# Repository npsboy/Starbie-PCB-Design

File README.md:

# Starbie

A small KiCad PCB project: a handheld board built around a Seeed XIAO ESP32-C3, with an I2C OLED display (128x64), an MPU6050 motion sensor (GY-521), and push buttons (Cherry MX switches).

## What is it?

The Starbie is a handheld PCB with an embedded OLED display that acts as a digital pet. You can interact with the digital character using push buttons and using the gyroscope (motion sensor), which can detect tilts, shakes and so on.

## What each part does:
- XIAO ESP32C3: The main brain of the system. This is a small development board, kind of like a regular esp 32 or raspberri-pi pico, not a bare microcontroller processor.
- OLED: The main screen that displays the charecter/pet.
- Accelerometer/Gyro: Detects tilts, shakes, etc.
- Temperature and humidity sensor: Exactly what it says it does. Can be used later to trigger different animations for the pet based on the environmental conditions.
- Mechanical keyboard switches: These are the two push buttons that help us interact with the pet. These are not the standard push buttons that you usually see, though.
- MX Keycaps: The keyboard switches do not come with a keycap. You have to buy and attach it yourself, or clicking the buttons won't be very comfortable.

## Schematic

## 3D Render

## Bill of Materials

Full BOM with vendor links and notes: [Starbie_BOM.csv](Starbie_BOM.csv) (prices in USD, vendors in India).

| Part | Ref | Purpose | Qty | UNIT | Vendor |
| --- | --- | --- | --- | --- | --- |
| Seeed Studio XIAO ESP32C3 | U2 | Microcontroller (Wi-Fi, main loop) | 1 | 15.91 | [Amazon](https://www.amazon.in/dp/B0B94JZ2YF) |
| 0.96in 128x64 I2C OLED, 4-pin | J1 | Shows the pet and the menu | 1 | 1.68 | [Ktron](https://www.ktron.in/product/oled-display-i2c-0-96-inch/) |
| MPU6050 GY-521 accelerometer/gyro | J2 | Tilt to steer the menu, shake detection | 1 | 1.99 | [Ktron](https://www.ktron.in/product/mpu6050-module/) |
| DHT11 temperature/humidity sensor, bare 4-pin | U1 | Senses room temperature and humidity | 1 | 0.96 | [Ktron](https://www.ktron.in/product/dht11-temperature-and-humidity-sensor/) |
| MX-style mechanical keyboard switches | SW1, SW2 | The two buttons (menu and stats) | 1 pack | 8.28 | [Amazon](https://www.amazon.in/dp/B0G39H2G4H) |
| Blank MX keycaps | SW1, SW2 | Caps for the two buttons | 1 pack | 7.18 | [Amazon](https://www.amazon.in/dp/B0HD587C9N) |
| PCB fabrication, 2-layer FR4, 98.04x98.8 mm | | The bare Starbie board (Rs 2,166 for 5 boards, about Rs 433 each) | 1 order (5 boards) | 22.45 | [LionCircuits](https://www.lioncircuits.com/) |

## Contents

- `Starbie.kicad_sch` / `Starbie.kicad_pcb` / `Starbie.kicad_pro`: KiCad project files
- `libs/`: custom symbols, footprints and 3D models
- `gerbers/`, `Starbie_Gerbers.zip`: manufacturing outputs
- `Starbie_BOM.csv`: bill of materials with vendors and prices (India)
- `Starbie_CPL.csv`: component placement list for PCB assembly
- `renders/`: top and bottom board renders

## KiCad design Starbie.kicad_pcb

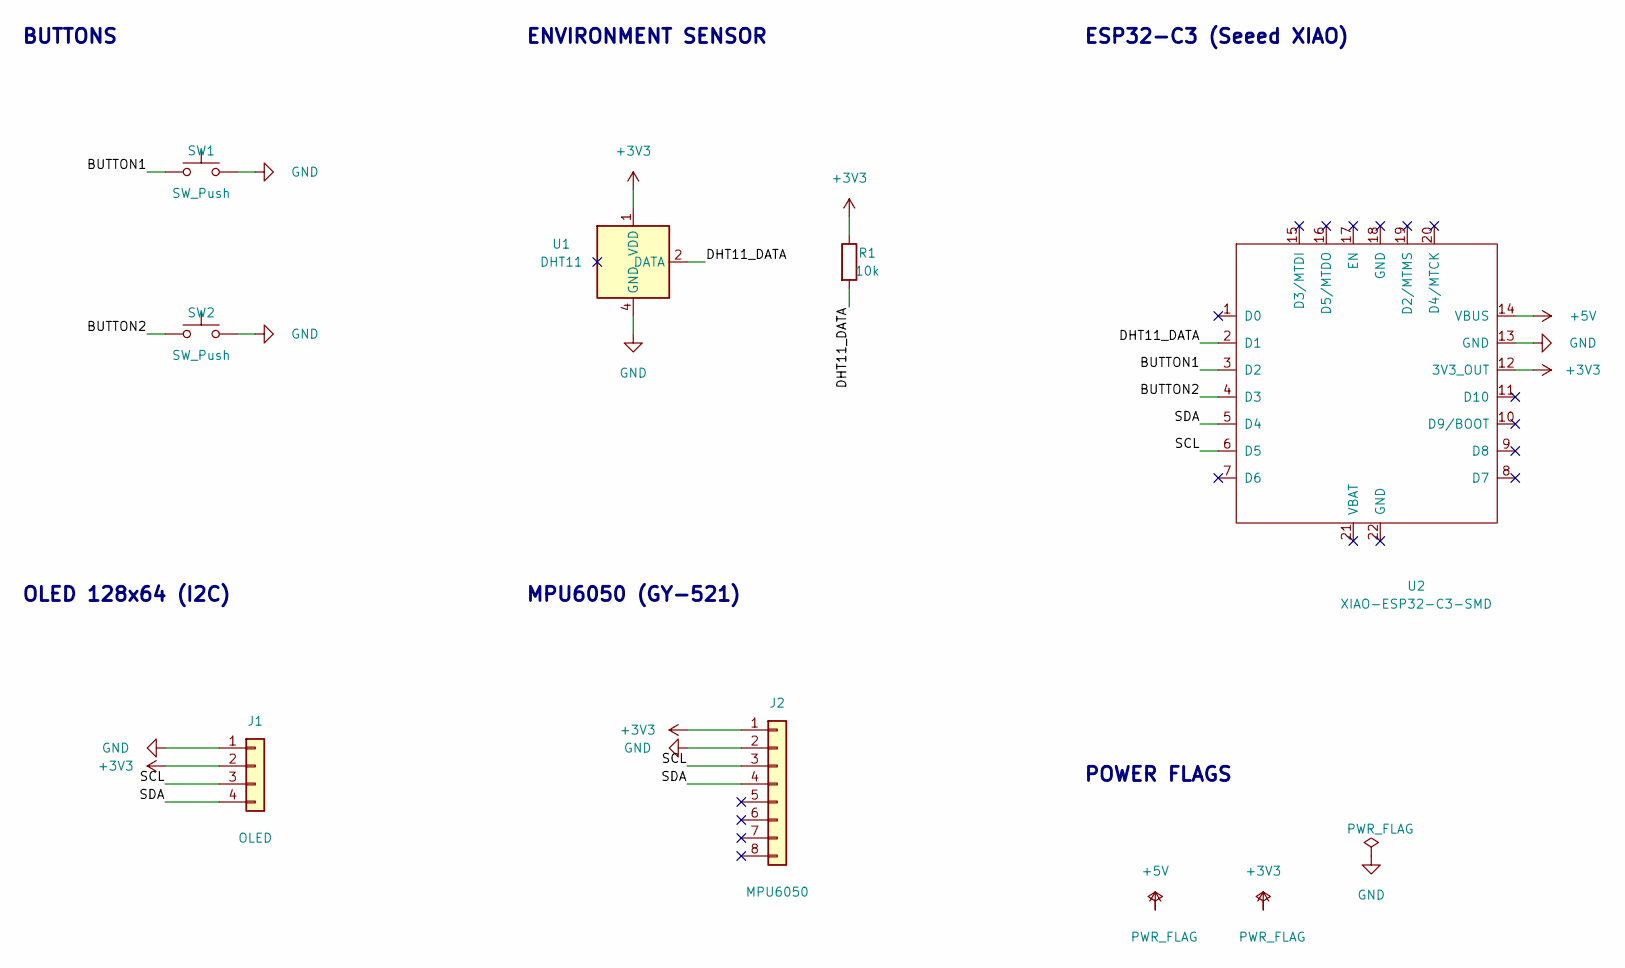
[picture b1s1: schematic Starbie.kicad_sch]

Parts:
J1: OLED; Display_128x64_096_I2C
J2: MPU6050; MPU6050_Module
R1: 10k; R_Axial_DIN0204_L3.6mm_D1.6mm_P7.62mm_Horizontal
SW1, SW2: SW_Push; SW_Cherry_MX_1.00u_PCB
U1: DHT11; Aosong_DHT11_5.5x12.0_P2.54mm
U2: XIAO-ESP32-C3-SMD

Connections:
+3V3: J1.2, J2.1, R1.1, U1.1 (VDD), U2.12 (3V3_OUT)
+5V: U2.14 (VBUS)
/BUTTON1: SW1.1, U2.3 (D2)
/BUTTON2: SW2.1, U2.4 (D3)
/DHT11_DATA: R1.2, U1.2 (DATA), U2.2 (D1)
/SCL: J1.3, J2.3, U2.6 (D5)
/SDA: J1.4, J2.4, U2.5 (D4)
GND: J1.1, J2.2, SW1.2, SW2.2, U1.4 (GND), U2.13 (GND)

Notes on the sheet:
ESP32-C3 (Seeed XIAO)
BUTTONS
ENVIRONMENT SENSOR
OLED 128x64 (I2C)
MPU6050 (GY-521)
POWER FLAGS

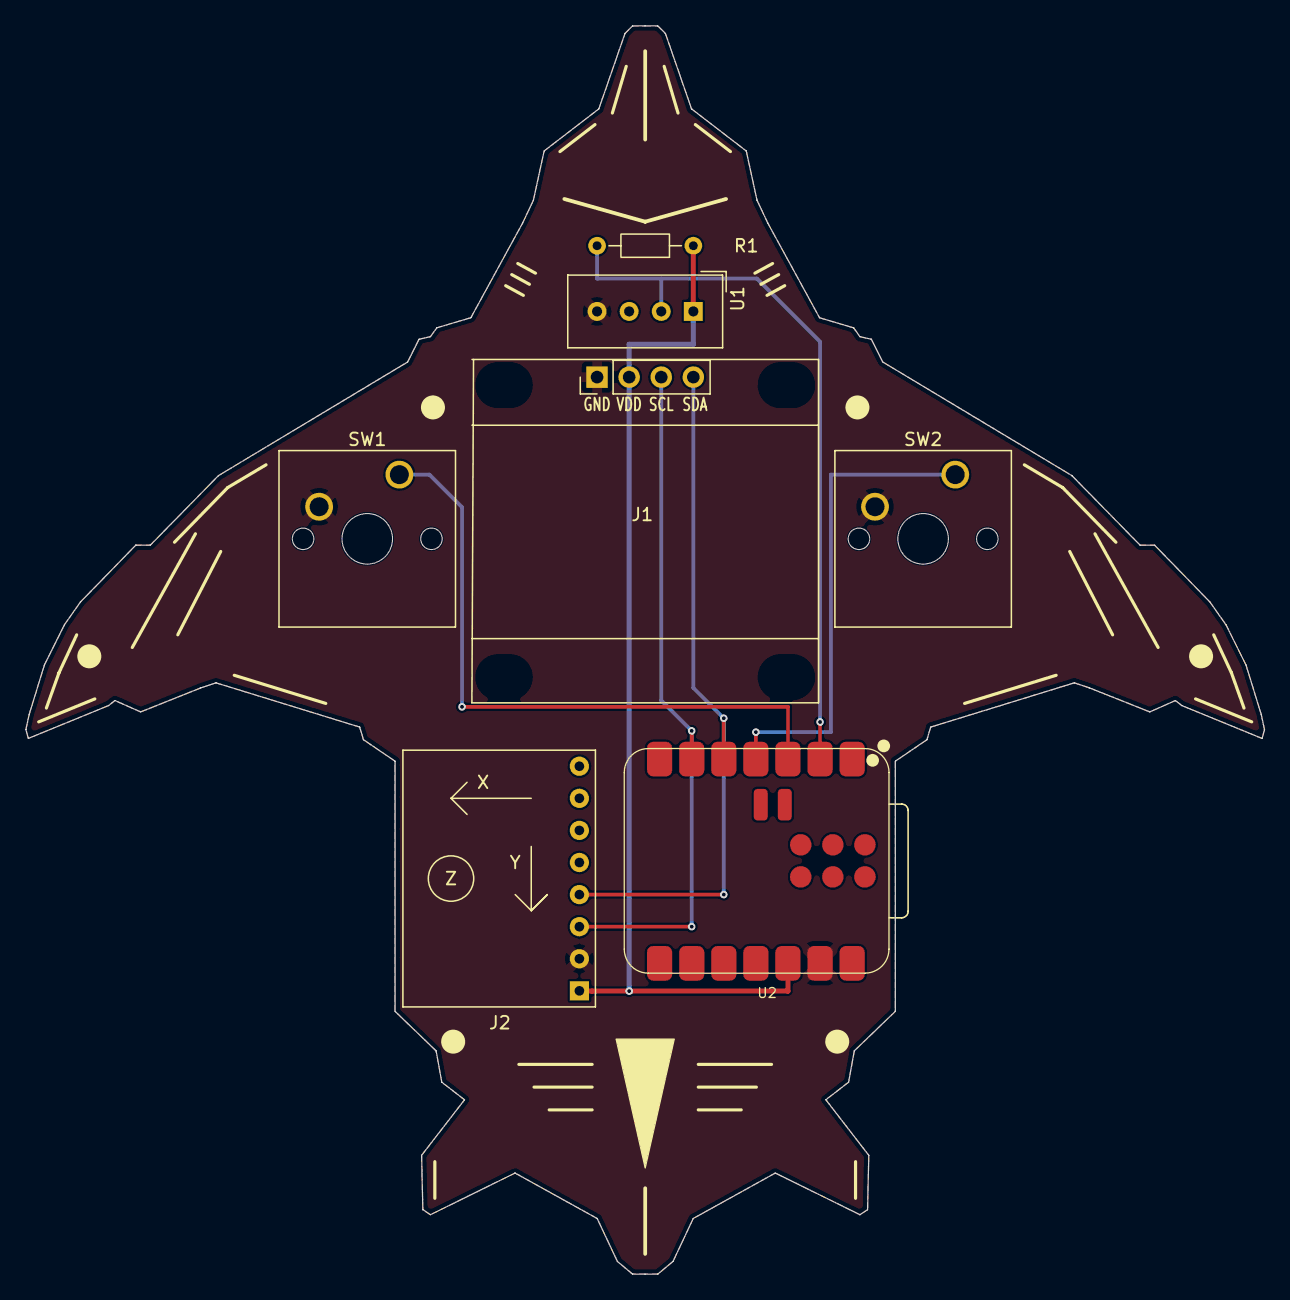
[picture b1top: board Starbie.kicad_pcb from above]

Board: 2 copper layers, 98.0 x 98.8 mm, 7 parts (0 on the bottom side), 7 nets.
